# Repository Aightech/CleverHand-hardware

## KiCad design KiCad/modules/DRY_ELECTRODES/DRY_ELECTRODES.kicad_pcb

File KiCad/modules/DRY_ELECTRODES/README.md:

# Dry Electrodes Module
This module is responsible for interfacing the sensors/actuators inputs/outputs with the user skin or with other modules.

## Electrical Schematic

## PCB Layout

## 3D Model

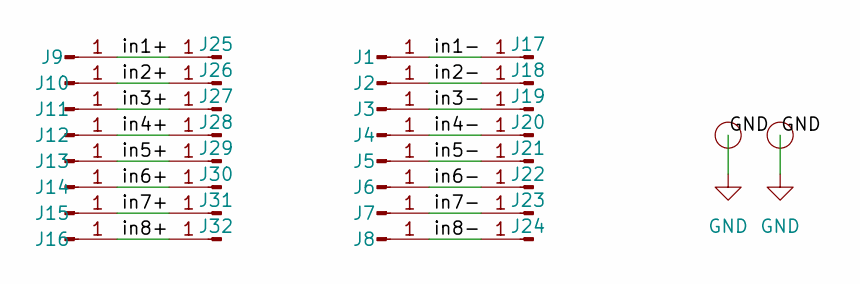
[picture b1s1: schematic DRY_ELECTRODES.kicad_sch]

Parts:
I3, I4: smd_insert; insert_1.2mm
J1, J2, J3, J4, J5, J6, J7, J8, J9, J10, J11, J12, J13, J14, J15, J16: Conn_01x01_Pin; SolderWirePad_1x01_SMD_1x2mm
J17, J18, J19, J20, J21, J22, J23, J24, J25, J26, J27, J28, J29, J30, J31, J32: Conn_01x01_Pin; Pin_D1.2mm_pogo

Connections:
/in1+: J9.1, J25.1
/in1-: J1.1, J17.1
/in2+: J10.1, J26.1
/in2-: J2.1, J18.1
/in3+: J11.1, J27.1
/in3-: J3.1, J19.1
/in4+: J12.1, J28.1
/in4-: J4.1, J20.1
/in5+: J13.1, J29.1
/in5-: J5.1, J21.1
/in6+: J14.1, J30.1
/in6-: J6.1, J22.1
/in7+: J15.1, J31.1
/in7-: J7.1, J23.1
/in8+: J16.1, J32.1
/in8-: J8.1, J24.1
GND: I3.1 (conn), I4.1 (conn)

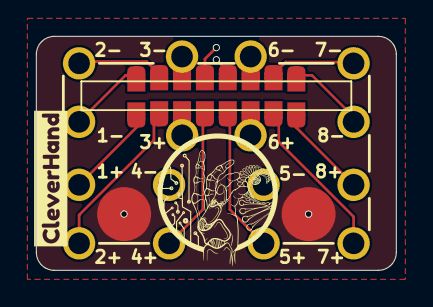
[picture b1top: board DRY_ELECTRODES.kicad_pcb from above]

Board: 4 copper layers, 20.0 x 13.0 mm, 35 parts (0 on the bottom side), 17 nets.

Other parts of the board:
kibuzzard-660706DE: G***; kibuzzard-660706DE

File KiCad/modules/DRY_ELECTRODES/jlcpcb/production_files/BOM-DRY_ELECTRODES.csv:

Comment,Designator,Footprint,LCSC
Conn_01x01_Pin,J4,SolderWirePad_1x01_SMD_1x2mm,
Conn_01x01_Pin,J2,SolderWirePad_1x01_SMD_1x2mm,
Conn_01x01_Pin,J1,SolderWirePad_1x01_SMD_1x2mm,
Conn_01x01_Pin,J5,SolderWirePad_1x01_SMD_1x2mm,
Conn_01x01_Pin,J7,SolderWirePad_1x01_SMD_1x2mm,
Conn_01x01_Pin,J3,SolderWirePad_1x01_SMD_1x2mm,
Conn_01x01_Pin,J6,SolderWirePad_1x01_SMD_1x2mm,
Conn_01x01_Pin,J8,SolderWirePad_1x01_SMD_1x2mm,
smd_insert,I4,insert_1.2mm,
smd_insert,I3,insert_1.2mm,
Conn_01x01_Pin,J14,SolderWirePad_1x01_SMD_1x2mm,
Conn_01x01_Pin,J9,SolderWirePad_1x01_SMD_1x2mm,
Conn_01x01_Pin,J12,SolderWirePad_1x01_SMD_1x2mm,
Conn_01x01_Pin,J13,SolderWirePad_1x01_SMD_1x2mm,
Conn_01x01_Pin,J16,SolderWirePad_1x01_SMD_1x2mm,
Conn_01x01_Pin,J10,SolderWirePad_1x01_SMD_1x2mm,
Conn_01x01_Pin,J15,SolderWirePad_1x01_SMD_1x2mm,
Conn_01x01_Pin,J11,SolderWirePad_1x01_SMD_1x2mm,
Conn_01x01_Pin,J20,Pin_D1.2mm_pogo,
Conn_01x01_Pin,J23,Pin_D1.2mm_pogo,
Conn_01x01_Pin,J30,Pin_D1.2mm_pogo,
Conn_01x01_Pin,J27,Pin_D1.2mm_pogo,
Conn_01x01_Pin,J25,Pin_D1.2mm_pogo,
Conn_01x01_Pin,J31,Pin_D1.2mm_pogo,
Conn_01x01_Pin,J29,Pin_D1.2mm_pogo,
Conn_01x01_Pin,J32,Pin_D1.2mm_pogo,
Conn_01x01_Pin,J18,Pin_D1.2mm_pogo,
Conn_01x01_Pin,J22,Pin_D1.2mm_pogo,
Conn_01x01_Pin,J19,Pin_D1.2mm_pogo,
Conn_01x01_Pin,J21,Pin_D1.2mm_pogo,
Conn_01x01_Pin,J26,Pin_D1.2mm_pogo,
Conn_01x01_Pin,J17,Pin_D1.2mm_pogo,
Conn_01x01_Pin,J28,Pin_D1.2mm_pogo,
Conn_01x01_Pin,J24,Pin_D1.2mm_pogo,

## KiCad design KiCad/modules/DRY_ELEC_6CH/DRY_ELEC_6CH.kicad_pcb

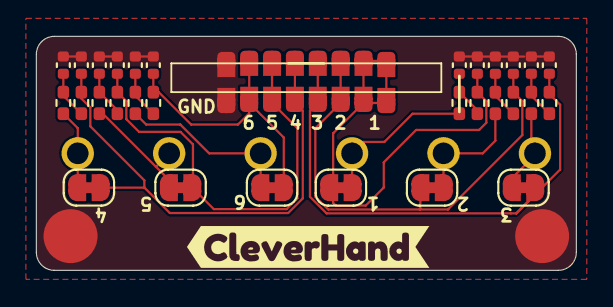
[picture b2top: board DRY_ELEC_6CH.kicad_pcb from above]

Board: 4 copper layers, 30.0 x 13.0 mm, 55 parts (0 on the bottom side), 19 nets.

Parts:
C1, C2, C3, C4, C5, C6, C7, C8, C9, C10, C11, C12: C; C_0402_1005Metric
I3, I4: smd_insert; insert_1.2mm
J1, J2, J3, J4, J5, J6, J7, J8, J9, J10, J11, J12, J13, J14, J15, J16: Conn_01x01_Pin; SolderWirePad_1x01_SMD_1x2mm
J17, J18, J19, J20, J21, J22: Conn_01x01_Pin; Pin_D1.2mm_pogo
JP1, JP2, JP3, JP4, JP5, JP6: SolderJumper_2_Bridged; SolderJumper-2_P1.3mm_Bridged_RoundedPad1.0x1.5mm
R1, R2, R3, R4, R5, R6, R7, R8, R9, R10, R11, R12: R; R_0402_1005Metric_Pad0.72x0.64mm_HandSolder
kibuzzard-66BA2E59: G***; kibuzzard-66BA2E59

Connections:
/IN1: C2.1, J7.1, J8.1, J15.1, J16.1, JP1.2 (B), R2.2
/IN2: C4.1, J6.1, J14.1, JP2.2 (B), R4.2
/IN3: C6.1, J5.1, J13.1, JP3.2 (B), R6.2
/IN4: C8.1, J4.1, J12.1, JP4.2 (B), R8.2
/IN5: C10.1, J3.1, J11.1, JP5.2 (B), R10.2
/IN6: C12.1, J2.1, J10.1, JP6.2 (B), R12.2
/filtering_1/ELECTRODE: J17.1, JP1.1 (A), R1.1
/filtering_2/ELECTRODE: J18.1, JP2.1 (A), R3.1
/filtering_3/ELECTRODE: J19.1, JP3.1 (A), R5.1
/filtering_4/ELECTRODE: J20.1, JP4.1 (A), R7.1
/filtering_5/ELECTRODE: J21.1, JP5.1 (A), R9.1
/filtering_6/ELECTRODE: J22.1, JP6.1 (A), R11.1
GND: C1.2, C2.2, C3.2, C4.2, C5.2, C6.2, C7.2, C8.2, C9.2, C10.2, C11.2, C12.2, I3.1 (conn), I4.1 (conn), J1.1, J9.1
unnamed: C1.1, R1.2, R2.1
unnamed: C3.1, R3.2, R4.1
unnamed: C5.1, R5.2, R6.1
unnamed: C7.1, R7.2, R8.1
unnamed: C9.1, R9.2, R10.1
unnamed: C11.1, R11.2, R12.1

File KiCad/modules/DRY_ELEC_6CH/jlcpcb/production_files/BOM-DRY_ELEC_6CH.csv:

Comment,Designator,Footprint,LCSC
Conn_01x01_Pin,J14,SolderWirePad_1x01_SMD_1x2mm,
Conn_01x01_Pin,J4,SolderWirePad_1x01_SMD_1x2mm,
C,C9,C_0402_1005Metric,
smd_insert,I4,insert_1.2mm,
R,R6,R_0402_1005Metric_Pad0.72x0.64mm_HandSolder,
C,C2,C_0402_1005Metric,
Conn_01x01_Pin,J9,SolderWirePad_1x01_SMD_1x2mm,
C,C5,C_0402_1005Metric,
Conn_01x01_Pin,J2,SolderWirePad_1x01_SMD_1x2mm,
smd_insert,I3,insert_1.2mm,
C,C8,C_0402_1005Metric,
Conn_01x01_Pin,J17,Pin_D1.2mm_pogo,
R,R7,R_0402_1005Metric_Pad0.72x0.64mm_HandSolder,
Conn_01x01_Pin,J21,Pin_D1.2mm_pogo,
R,R12,R_0402_1005Metric_Pad0.72x0.64mm_HandSolder,
C,C4,C_0402_1005Metric,
Conn_01x01_Pin,J12,SolderWirePad_1x01_SMD_1x2mm,
R,R9,R_0402_1005Metric_Pad0.72x0.64mm_HandSolder,
Conn_01x01_Pin,J13,SolderWirePad_1x01_SMD_1x2mm,
Conn_01x01_Pin,J16,SolderWirePad_1x01_SMD_1x2mm,
C,C1,C_0402_1005Metric,
R,R11,R_0402_1005Metric_Pad0.72x0.64mm_HandSolder,
R,R10,R_0402_1005Metric_Pad0.72x0.64mm_HandSolder,
C,C6,C_0402_1005Metric,
R,R2,R_0402_1005Metric_Pad0.72x0.64mm_HandSolder,
R,R4,R_0402_1005Metric_Pad0.72x0.64mm_HandSolder,
Conn_01x01_Pin,J1,SolderWirePad_1x01_SMD_1x2mm,
C,C7,C_0402_1005Metric,
C,C3,C_0402_1005Metric,
R,R1,R_0402_1005Metric_Pad0.72x0.64mm_HandSolder,
Conn_01x01_Pin,J10,SolderWirePad_1x01_SMD_1x2mm,
Conn_01x01_Pin,J15,SolderWirePad_1x01_SMD_1x2mm,
R,R8,R_0402_1005Metric_Pad0.72x0.64mm_HandSolder,
Conn_01x01_Pin,J20,Pin_D1.2mm_pogo,
C,C11,C_0402_1005Metric,
Conn_01x01_Pin,J5,SolderWirePad_1x01_SMD_1x2mm,
C,C12,C_0402_1005Metric,
Conn_01x01_Pin,J7,SolderWirePad_1x01_SMD_1x2mm,
Conn_01x01_Pin,J3,SolderWirePad_1x01_SMD_1x2mm,
Conn_01x01_Pin,J18,Pin_D1.2mm_pogo,
C,C10,C_0402_1005Metric,
Conn_01x01_Pin,J22,Pin_D1.2mm_pogo,
R,R3,R_0402_1005Metric_Pad0.72x0.64mm_HandSolder,
Conn_01x01_Pin,J19,Pin_D1.2mm_pogo,
Conn_01x01_Pin,J11,SolderWirePad_1x01_SMD_1x2mm,
Conn_01x01_Pin,J6,SolderWirePad_1x01_SMD_1x2mm,
Conn_01x01_Pin,J8,SolderWirePad_1x01_SMD_1x2mm,
R,R5,R_0402_1005Metric_Pad0.72x0.64mm_HandSolder,

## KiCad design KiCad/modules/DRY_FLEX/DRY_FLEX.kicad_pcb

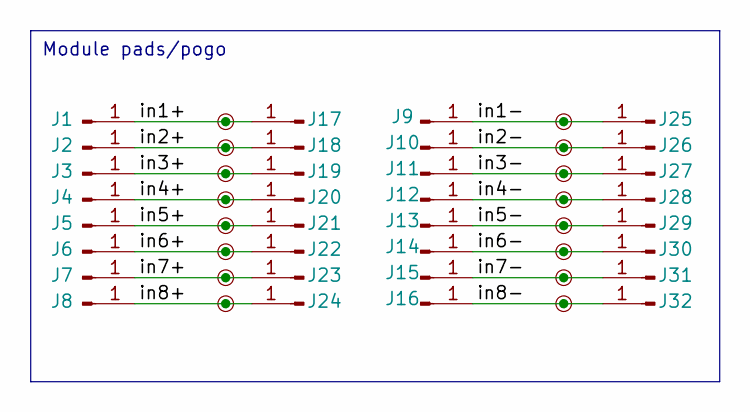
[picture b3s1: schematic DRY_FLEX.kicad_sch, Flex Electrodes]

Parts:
J1, J2, J3, J4, J5, J6, J7, J8, J9, J10, J11, J12, J13, J14, J15, J16, J17, J18, J19, J20, J21, J22, J23, J24, J25, J26, J27, J28, J29, J30, J31, J32: Conn_01x01_Pin; Pin_D1.2mm_pogo
TP1, TP2, TP3, TP4, TP5, TP6, TP7, TP8, TP9, TP10, TP11, TP12, TP13, TP14, TP15, TP16: TestPoint; SolderWirePad_1x01_SMD_1x2mm

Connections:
/in1+: J1.1, J17.1, TP9.1
/in1-: J9.1, J25.1, TP1.1
/in2+: J2.1, J18.1, TP10.1
/in2-: J10.1, J26.1, TP2.1
/in3+: J3.1, J19.1, TP11.1
/in3-: J11.1, J27.1, TP3.1
/in4+: J4.1, J20.1, TP12.1
/in4-: J12.1, J28.1, TP4.1
/in5+: J5.1, J21.1, TP13.1
/in5-: J13.1, J29.1, TP5.1
/in6+: J6.1, J22.1, TP14.1
/in6-: J14.1, J30.1, TP6.1
/in7+: J7.1, J23.1, TP15.1
/in7-: J15.1, J31.1, TP7.1
/in8+: J8.1, J24.1, TP16.1
/in8-: J16.1, J32.1, TP8.1

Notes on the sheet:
Module pads/pogo

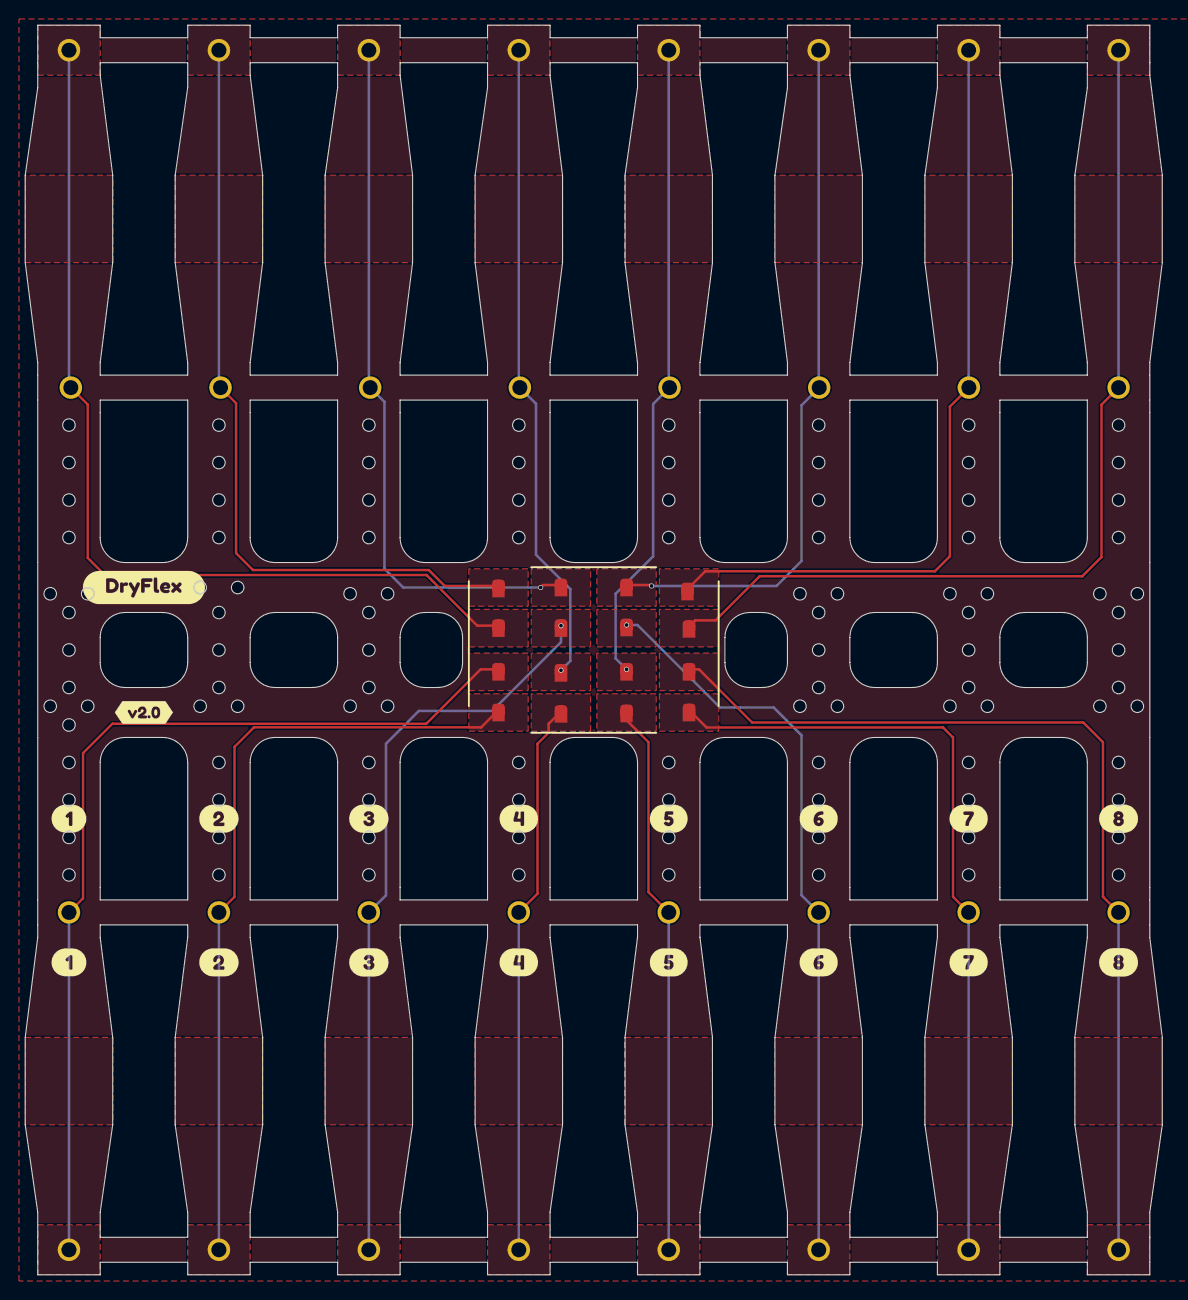
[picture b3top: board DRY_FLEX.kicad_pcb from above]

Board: 2 copper layers, 91.0 x 100.0 mm, 67 parts (1 on the bottom side), 16 nets.

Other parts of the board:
kibuzzard-658EC94F, kibuzzard-658EC94F#2: G***; kibuzzard-658EC94F
kibuzzard-658EC95B, kibuzzard-658EC95B#2: G***; kibuzzard-658EC95B
kibuzzard-658EC936, kibuzzard-658EC936#2: G***; kibuzzard-658EC936
kibuzzard-658EC955, kibuzzard-658EC955#2: G***; kibuzzard-658EC955
kibuzzard-658EC960, kibuzzard-658EC960#2: G***; kibuzzard-658EC960
kibuzzard-66085B0B, kibuzzard-66085B0B#2: G***; kibuzzard-66085B0B
kibuzzard-66085B03, kibuzzard-66085B03#2: G***; kibuzzard-66085B03
kibuzzard-66085B10, kibuzzard-66085B10#2: G***; kibuzzard-66085B10
kibuzzard-66085C02: G***; kibuzzard-66085C02
kibuzzard-660866D6: G***; kibuzzard-660866D6
kibuzzard-6608669B: G***; kibuzzard-6608669B

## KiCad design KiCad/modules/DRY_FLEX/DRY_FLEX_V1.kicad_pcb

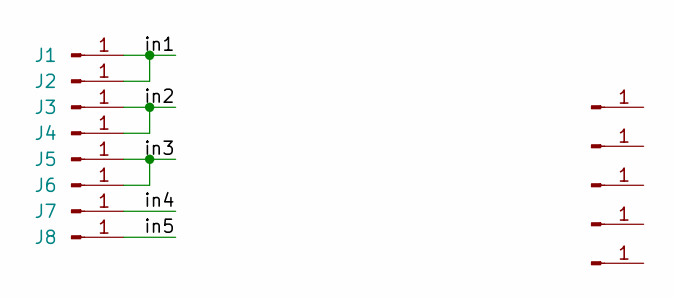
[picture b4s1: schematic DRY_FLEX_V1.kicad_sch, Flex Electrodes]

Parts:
J1, J2, J3, J4, J5, J6, J7, J8: Conn_01x01_Pin; SolderWirePad_1x01_SMD_1x2mm
J9, J10, J11, J12, J13: Conn_01x01_Pin; PinHeader_1x01_P2.54mm_Vertical

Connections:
/in1: J1.1, J2.1
/in2: J3.1, J4.1
/in3: J5.1, J6.1
/in4: J7.1
/in5: J8.1

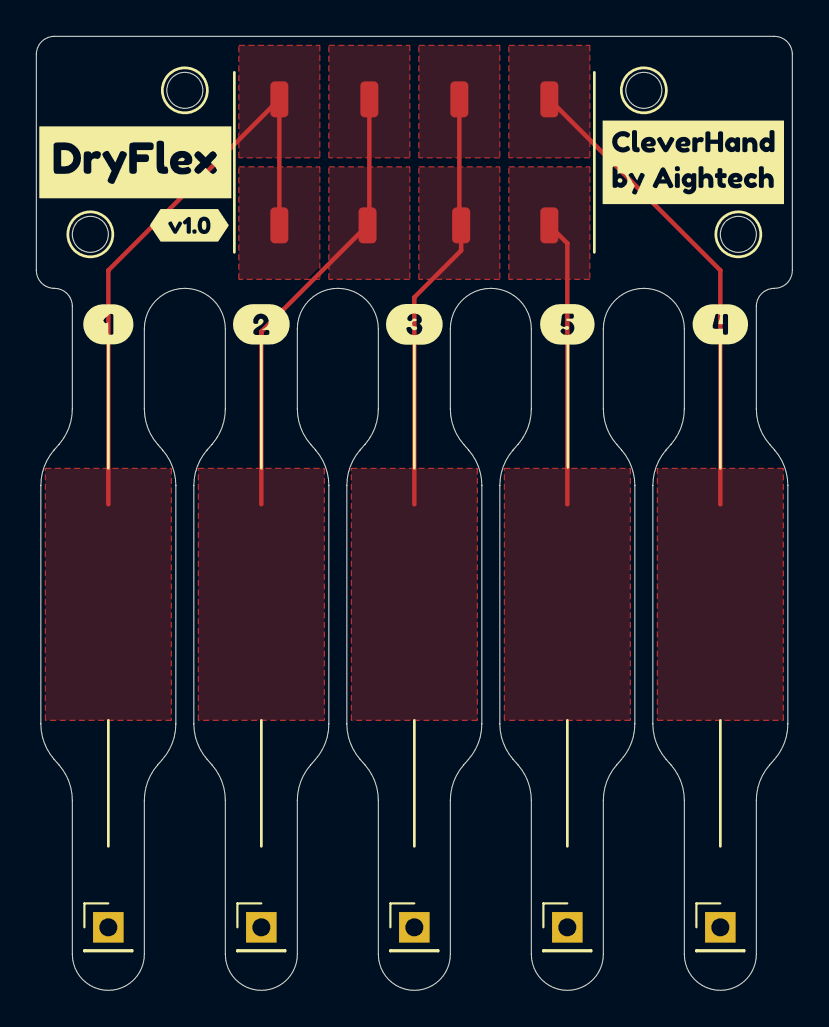
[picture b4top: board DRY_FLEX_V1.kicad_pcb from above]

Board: 2 copper layers, 42.0 x 53.0 mm, 21 parts (0 on the bottom side), 3 nets.

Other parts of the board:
kibuzzard-658EC94F: G***; kibuzzard-658EC94F
kibuzzard-658EC95B: G***; kibuzzard-658EC95B
kibuzzard-658EC834: G***; kibuzzard-658EC834
kibuzzard-658EC936: G***; kibuzzard-658EC936
kibuzzard-658EC955: G***; kibuzzard-658EC955
kibuzzard-658EC960: G***; kibuzzard-658EC960
kibuzzard-65902AA8: G***; kibuzzard-65902AA8
kibuzzard-65902ADF: G***; kibuzzard-65902ADF
